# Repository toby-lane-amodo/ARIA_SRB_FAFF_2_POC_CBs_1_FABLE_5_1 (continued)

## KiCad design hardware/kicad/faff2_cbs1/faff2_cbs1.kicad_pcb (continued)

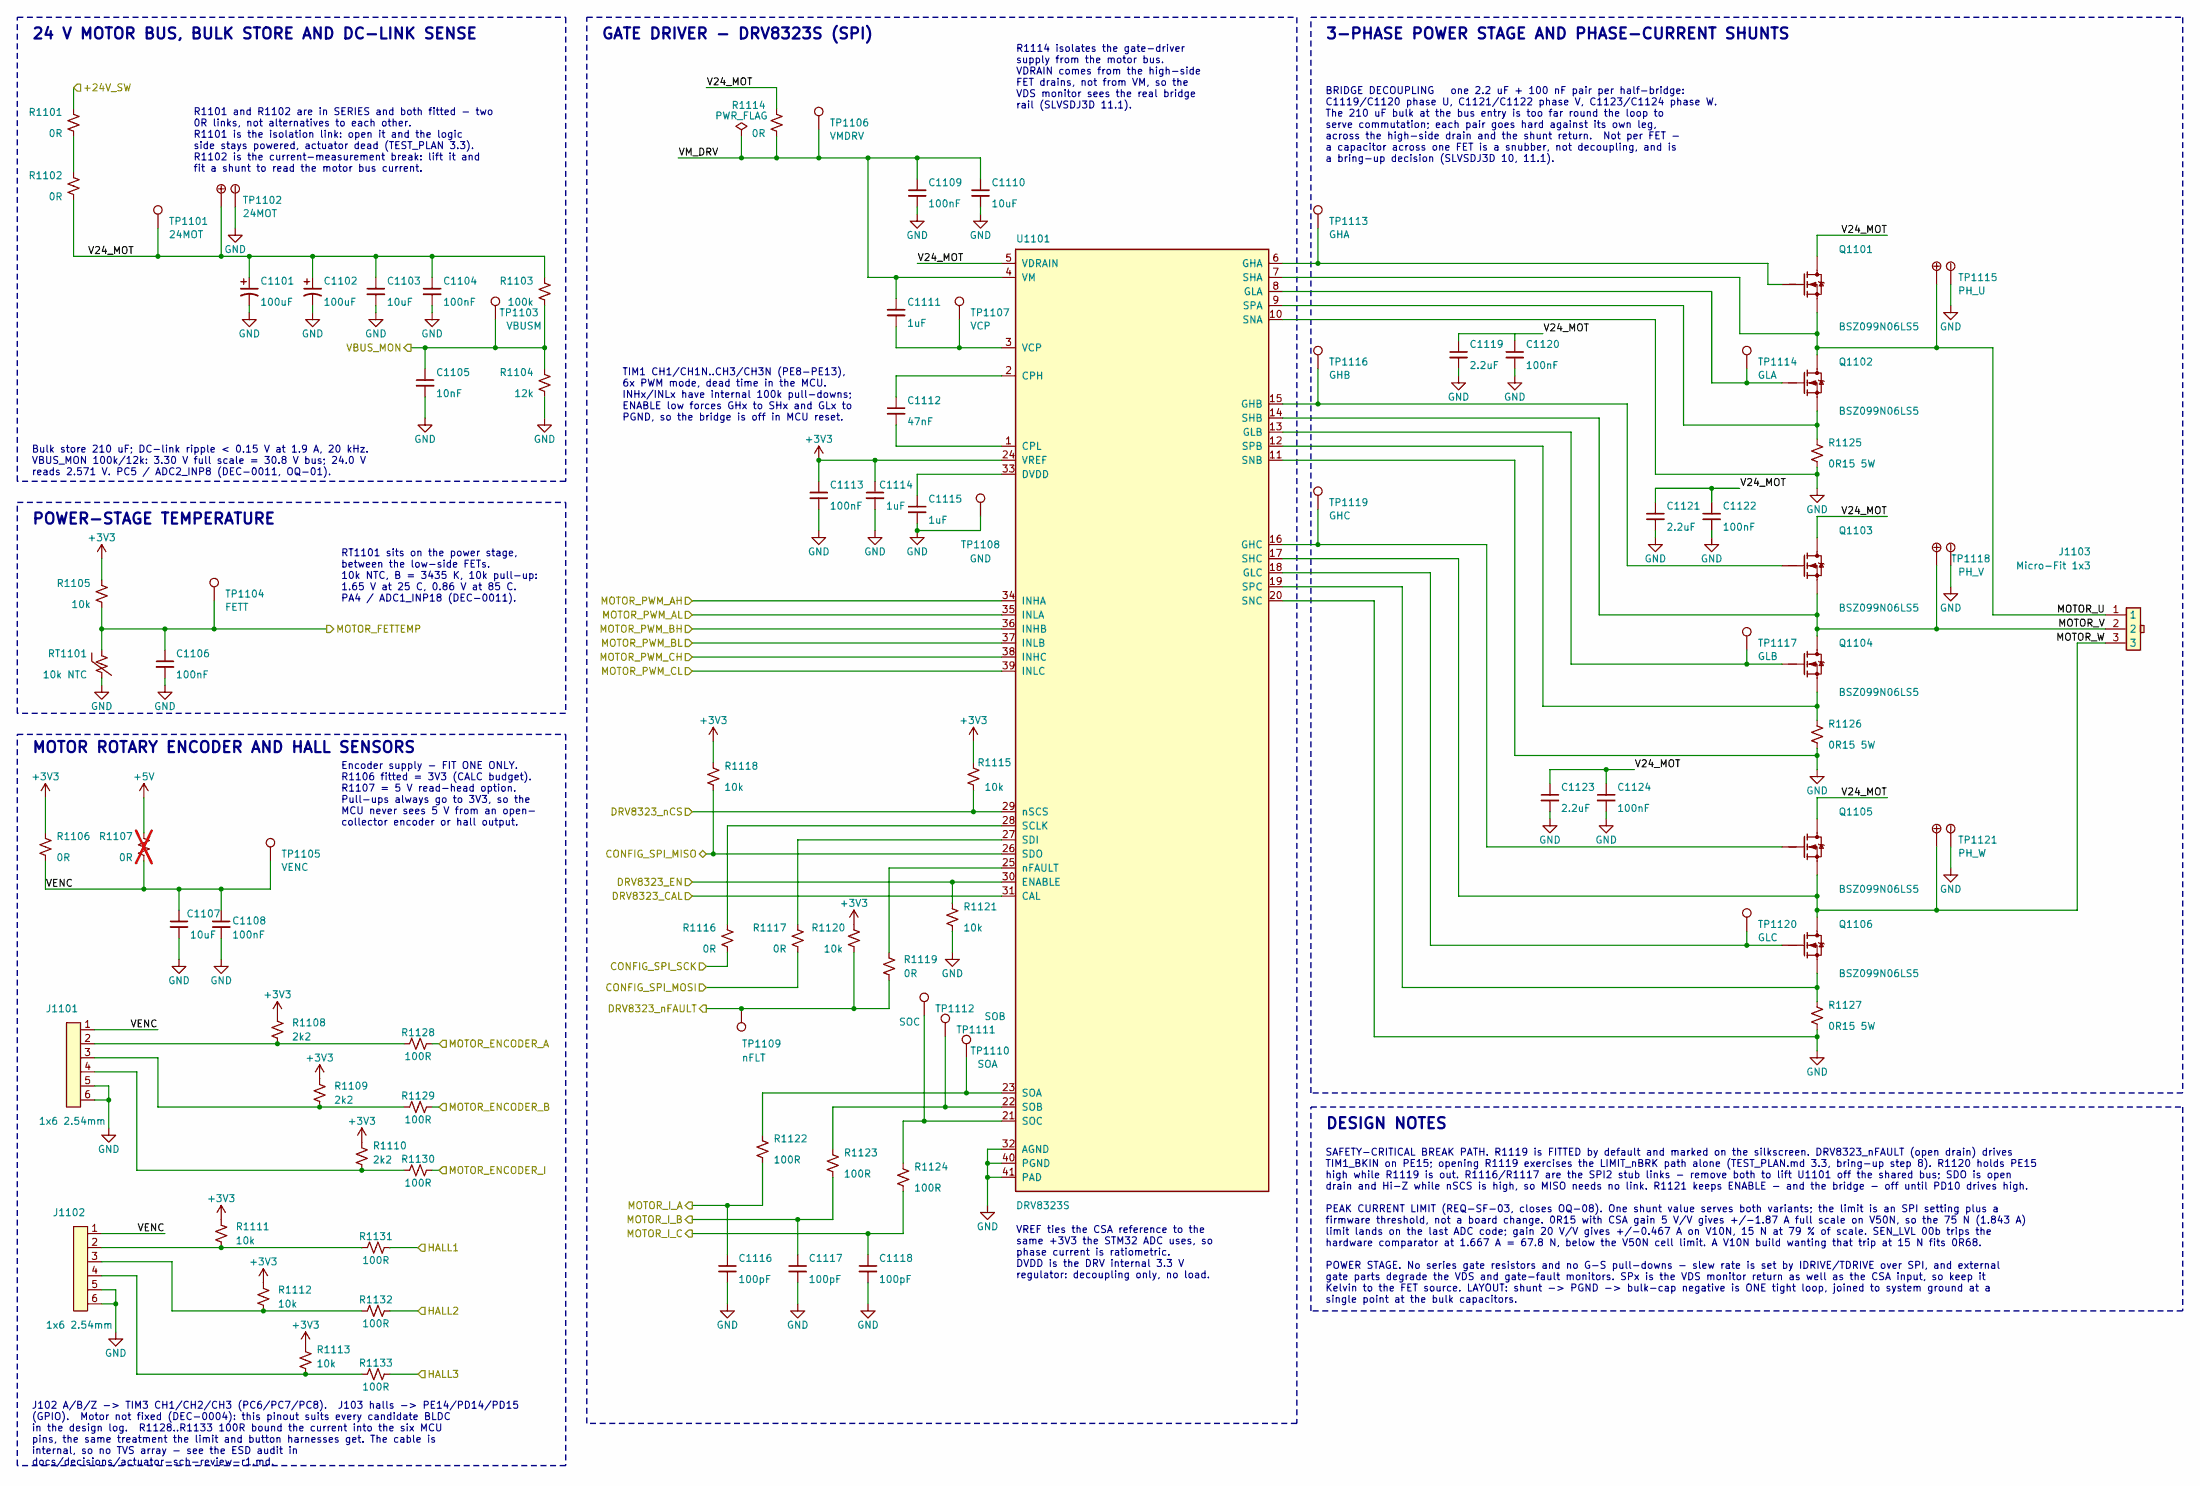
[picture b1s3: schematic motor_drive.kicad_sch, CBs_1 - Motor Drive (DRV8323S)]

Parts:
C1101, C1102: 100uF; C_ALU_D10_L10.2_SMT_ANTI-VIBE
C1103, C1110: 10uF; C_1210_3225Metric
C1104, C1109: 100nF; C_0805_2012Metric
C1105: 10nF; C_0603_1608Metric
C1106, C1108, C1113: 100nF; C_0402_1005Metric
C1107: 10uF; C_0805_2012Metric
C1111, C1114, C1115: 1uF; C_0603_1608Metric
C1112: 47nF; C_0603_1608Metric
C1116, C1117, C1118: 100pF; C_0603_1608Metric
C1119, C1121, C1123: 2.2uF; C_1206_3216Metric; mpn KAM31GR72A225KU
C1120, C1122, C1124: 100nF; C_0805_2012Metric; Voltage 100V; mpn 08051C104K4T4A
J1101, J1102: 1x6 2.54mm; Adam_Tech_PH1-06-UA
J1103: Micro-Fit 1x3; 436500327
Q1101, Q1102, Q1103, Q1104, Q1105, Q1106: BSZ099N06LS5; PG-TSDSON-8-32
R1101, R1102, R1114: 0R; R_1206_3216Metric
R1103: 100k; R_0603_1608Metric
R1104: 12k; R_0603_1608Metric
R1105, R1111, R1112, R1113, R1115, R1118, R1120, R1121: 10k; R_0603_1608Metric
R1106, R1116, R1117, R1119: 0R; R_0603_1608Metric
R1107: 0R; R_0603_1608Metric; not fitted
R1108, R1109, R1110: 2k2; R_0603_1608Metric
R1122, R1123, R1124: 100R; R_0603_1608Metric
R1125, R1126, R1127: 0R15 5W; R_4527_11470Metric
R1128, R1129, R1130, R1131, R1132, R1133: 100R; R_0603_1608Metric; mpn ERJ-3EKF1000V
RT1101: 10k NTC; R_0603_1608Metric
TP1101: 24MOT; TestPoint_Pad_D1.0mm
TP1102: 24MOT; TestPoint_Dual_D1.5mm_H1.0mm
TP1103: VBUSM; TestPoint_Pad_D1.0mm
TP1104: FETT; TestPoint_Pad_D1.0mm
TP1105: VENC; TestPoint_Pad_D1.0mm
TP1106: VMDRV; TestPoint_Pad_D1.0mm
TP1107: VCP; TestPoint_Pad_D1.0mm
TP1108: GND; TestPoint_Pad_D1.0mm
TP1109: nFLT; KeystoneMiniatureTestLoop
TP1110: SOA; KeystoneMiniatureTestLoop
TP1111: SOB; KeystoneMiniatureTestLoop
TP1112: SOC; KeystoneMiniatureTestLoop
TP1113: GHA; KeystoneMiniatureTestLoop
TP1114: GLA; KeystoneMiniatureTestLoop
TP1115: PH_U; TestPoint_Dual_D1.5mm_H1.0mm
TP1116: GHB; KeystoneMiniatureTestLoop
TP1117: GLB; KeystoneMiniatureTestLoop
TP1118: PH_V; TestPoint_Dual_D1.5mm_H1.0mm
TP1119: GHC; KeystoneMiniatureTestLoop
TP1120: GLC; KeystoneMiniatureTestLoop
TP1121: PH_W; TestPoint_Dual_D1.5mm_H1.0mm
U1101: DRV8323S; Texas_RTA0040B_WQFN-40-1EP_6x6mm_P0.5mm_EP4.15x4.15mm

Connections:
+3V3: C1113.1, C1114.1, R1105.1, R1106.1, R1108.1, R1109.1, R1110.1, R1111.1, R1112.1, R1113.1, R1115.1, R1118.1, R1120.1, U1101.24 (VREF); also elsewhere on the board
+5V: R1107.1; also elsewhere on the board
/mcu/DRV8323_CAL: U1101.31 (CAL); also elsewhere on the board
/mcu/DRV8323_EN: R1121.1, U1101.30 (ENABLE); also elsewhere on the board
/mcu/DRV8323_nCS: R1115.2, U1101.29 (nSCS); also elsewhere on the board
/mcu/DRV8323_nFAULT: R1119.2, R1120.2, TP1109.1; also elsewhere on the board
/mcu/HALL1: R1131.2; also elsewhere on the board
/mcu/HALL2: R1132.2; also elsewhere on the board
/mcu/HALL3: R1133.2; also elsewhere on the board
/mcu/MOTOR_ENCODER_A: R1128.2; also elsewhere on the board
/mcu/MOTOR_ENCODER_B: R1129.2; also elsewhere on the board
/mcu/MOTOR_ENCODER_I: R1130.2; also elsewhere on the board
/mcu/MOTOR_FETTEMP: C1106.1, R1105.2, RT1101.1, TP1104.1; also elsewhere on the board
/mcu/MOTOR_I_A: C1116.1, R1122.2; also elsewhere on the board
/mcu/MOTOR_I_B: C1117.1, R1123.2; also elsewhere on the board
/mcu/MOTOR_I_C: C1118.1, R1124.2; also elsewhere on the board
/mcu/MOTOR_PWM_AH: U1101.34 (INHA); also elsewhere on the board
/mcu/MOTOR_PWM_AL: U1101.35 (INLA); also elsewhere on the board
/mcu/MOTOR_PWM_BH: U1101.36 (INHB); also elsewhere on the board
/mcu/MOTOR_PWM_BL: U1101.37 (INLB); also elsewhere on the board
/mcu/MOTOR_PWM_CH: U1101.38 (INHC); also elsewhere on the board
/mcu/MOTOR_PWM_CL: U1101.39 (INLC); also elsewhere on the board
/mcu/VBUS_MON: C1105.1, R1103.2, R1104.1, TP1103.1; also elsewhere on the board
/motor_drive/MOTOR_U: J1103.1, Q1101.1_2_3 (S_3), Q1102.5_6_7_8 (D_2), TP1115.1, U1101.7 (SHA)
/motor_drive/MOTOR_V: J1103.2, Q1103.1_2_3 (S_3), Q1104.5_6_7_8 (D_2), TP1118.1, U1101.14 (SHB)
/motor_drive/MOTOR_W: J1103.3, Q1105.1_2_3 (S_3), Q1106.5_6_7_8 (D_2), TP1121.1, U1101.17 (SHC)
/motor_drive/V24_MOT: C1101.1, C1102.1, C1103.1, C1104.1, C1119.1, C1120.1, C1121.1, C1122.1, C1123.1, C1124.1, Q1101.5_6_7_8 (D_2), Q1103.5_6_7_8 (D_2), Q1105.5_6_7_8 (D_2), R1102.2, R1103.1, R1114.1, TP1101.1, TP1102.1, U1101.5 (VDRAIN)
/motor_drive/VENC: C1107.1, C1108.1, J1101.1, J1102.1, R1106.2, R1107.2, TP1105.1
/motor_drive/VM_DRV: C1109.1, C1110.1, C1111.1, R1114.2, TP1106.1, U1101.4 (VM)
/power_entry_24v/+24V_SW: R1101.1; also elsewhere on the board
/temp_sense/CONFIG_SPI_MISO: R1118.2, U1101.26 (SDO); also elsewhere on the board
/temp_sense/CONFIG_SPI_MOSI: R1117.2; also elsewhere on the board
/temp_sense/CONFIG_SPI_SCK: R1116.2; also elsewhere on the board
GND: C1101.2, C1102.2, C1103.2, C1104.2, C1105.2, C1106.2, C1107.2, C1108.2, C1109.2, C1110.2, C1113.2, C1114.2, C1115.2, C1116.2, C1117.2, C1118.2, C1119.2, C1120.2, C1121.2, C1122.2, C1123.2, C1124.2, J1101.5, J1101.6, J1102.5, J1102.6, R1104.2, R1121.2, R1125.2, R1126.2, R1127.2, RT1101.2, TP1102.2, TP1108.1, TP1115.2, TP1118.2, TP1121.2, U1101.10 (SNA), U1101.11 (SNB), U1101.20 (SNC), U1101.32 (AGND), U1101.40 (PGND), U1101.41 (PAD); also elsewhere on the board
unnamed: J1101.2, R1108.2, R1128.1
unnamed: J1101.3, R1109.2, R1129.1
unnamed: J1101.4, R1110.2, R1130.1
unnamed: J1102.2, R1111.2, R1131.1
unnamed: J1102.3, R1112.2, R1132.1
unnamed: J1102.4, R1113.2, R1133.1
unnamed: Q1101.4 (G), TP1113.1, U1101.6 (GHA)
unnamed: Q1102.4 (G), TP1114.1, U1101.8 (GLA)
unnamed: Q1102.1_2_3 (S_3), R1125.1, U1101.9 (SPA)
unnamed: Q1103.4 (G), TP1116.1, U1101.15 (GHB)
unnamed: Q1104.4 (G), TP1117.1, U1101.13 (GLB)
unnamed: Q1104.1_2_3 (S_3), R1126.1, U1101.12 (SPB)
unnamed: Q1105.4 (G), TP1119.1, U1101.16 (GHC)
unnamed: Q1106.4 (G), TP1120.1, U1101.18 (GLC)
unnamed: Q1106.1_2_3 (S_3), R1127.1, U1101.19 (SPC)
unnamed: R1101.2, R1102.1
unnamed: C1112.1, U1101.2 (CPH)
unnamed: C1112.2, U1101.1 (CPL)
unnamed: C1115.1, U1101.33 (DVDD)
unnamed: R1116.1, U1101.28 (SCLK)
unnamed: R1117.1, U1101.27 (SDI)
unnamed: R1122.1, TP1110.1, U1101.23 (SOA)
unnamed: R1123.1, TP1111.1, U1101.22 (SOB)
unnamed: R1124.1, TP1112.1, U1101.21 (SOC)
unnamed: C1111.2, TP1107.1, U1101.3 (VCP)
unnamed: R1119.1, U1101.25 (nFAULT)

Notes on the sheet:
BRIDGE DECOUPLING one 2.2 uF + 100 nF pair per half-bridge: C1119/C1120 phase U, C1121/C1122 phase V, C1123/C1124 phase W. The 210 uF bulk at the bus entry is too far round the loop to serve commutation; each pair goes hard against its own leg, across the high-side drain and the shunt return. Not p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
Bulk store 210 uF; DC-link ripple < 0.15 V at 1.9 A, 20 kHz. VBUS_MON 100k/12k: 3.30 V full scale = 30.8 V bus; 24.0 V reads 2.571 V. PC5 / ADC2_INP8 (DEC-0011, OQ-01).
SAFETY-CRITICAL BREAK PATH. R1119 is FITTED by default and marked on the silkscreen. DRV8323_nFAULT (open drain) drives TIM1_BKIN on PE15; opening R1119 exercises the LIMIT_nBRK path alone (TEST_PLAN.md 3.3, bring-up step 8). R1120 holds PE15 high while R1119 is out. R1116/R1117 are the SPI2 stub l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
RT1101 sits on the power stage, between the low-side FETs. 10k NTC, B = 3435 K, 10k pull-up: 1.65 V at 25 C, 0.86 V at 85 C. PA4 / ADC1_INP18 (DEC-0011).
Encoder supply - FIT ONE ONLY. R1106 fitted = 3V3 (CALC budget). R1107 = 5 V read-head option. Pull-ups always go to 3V3, so the MCU never sees 5 V from an open- collector encoder or hall output.
J102 A/B/Z -> TIM3 CH1/CH2/CH3 (PC6/PC7/PC8). J103 halls -> PE14/PD14/PD15 (GPIO). Motor not fixed (DEC-0004): this pinout suits every candidate BLDC in the design log. R1128..R1133 100R bound the current into the six MCU pins, the same treatment the limit and button harnesses get. The cable is int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
MOTOR ROTARY ENCODER AND HALL SENSORS
R1101 and R1102 are in SERIES and both fitted - two 0R links, not alternatives to each other. R1101 is the isolation link: open it and the logic side stays powered, actuator dead (TEST_PLAN 3.3). R1102 is the current-measurement break: lift it and fit a shunt to read the motor bus current.
DESIGN NOTES
24 V MOTOR BUS, BULK STORE AND DC-LINK SENSE
TIM1 CH1/CH1N..CH3/CH3N (PE8-PE13), 6x PWM mode, dead time in the MCU. INHx/INLx have internal 100k pull-downs; ENABLE low forces GHx to SHx and GLx to PGND, so the bridge is off in MCU reset.
POWER-STAGE TEMPERATURE
VREF ties the CSA reference to the same +3V3 the STM32 ADC uses, so phase current is ratiometric. DVDD is the DRV internal 3.3 V regulator: decoupling only, no load.
R1114 isolates the gate-driver supply from the motor bus. VDRAIN comes from the high-side FET drains, not from VM, so the VDS monitor sees the real bridge rail (SLVSDJ3D 11.1).
GATE DRIVER - DRV8323S (SPI)
3-PHASE POWER STAGE AND PHASE-CURRENT SHUNTS

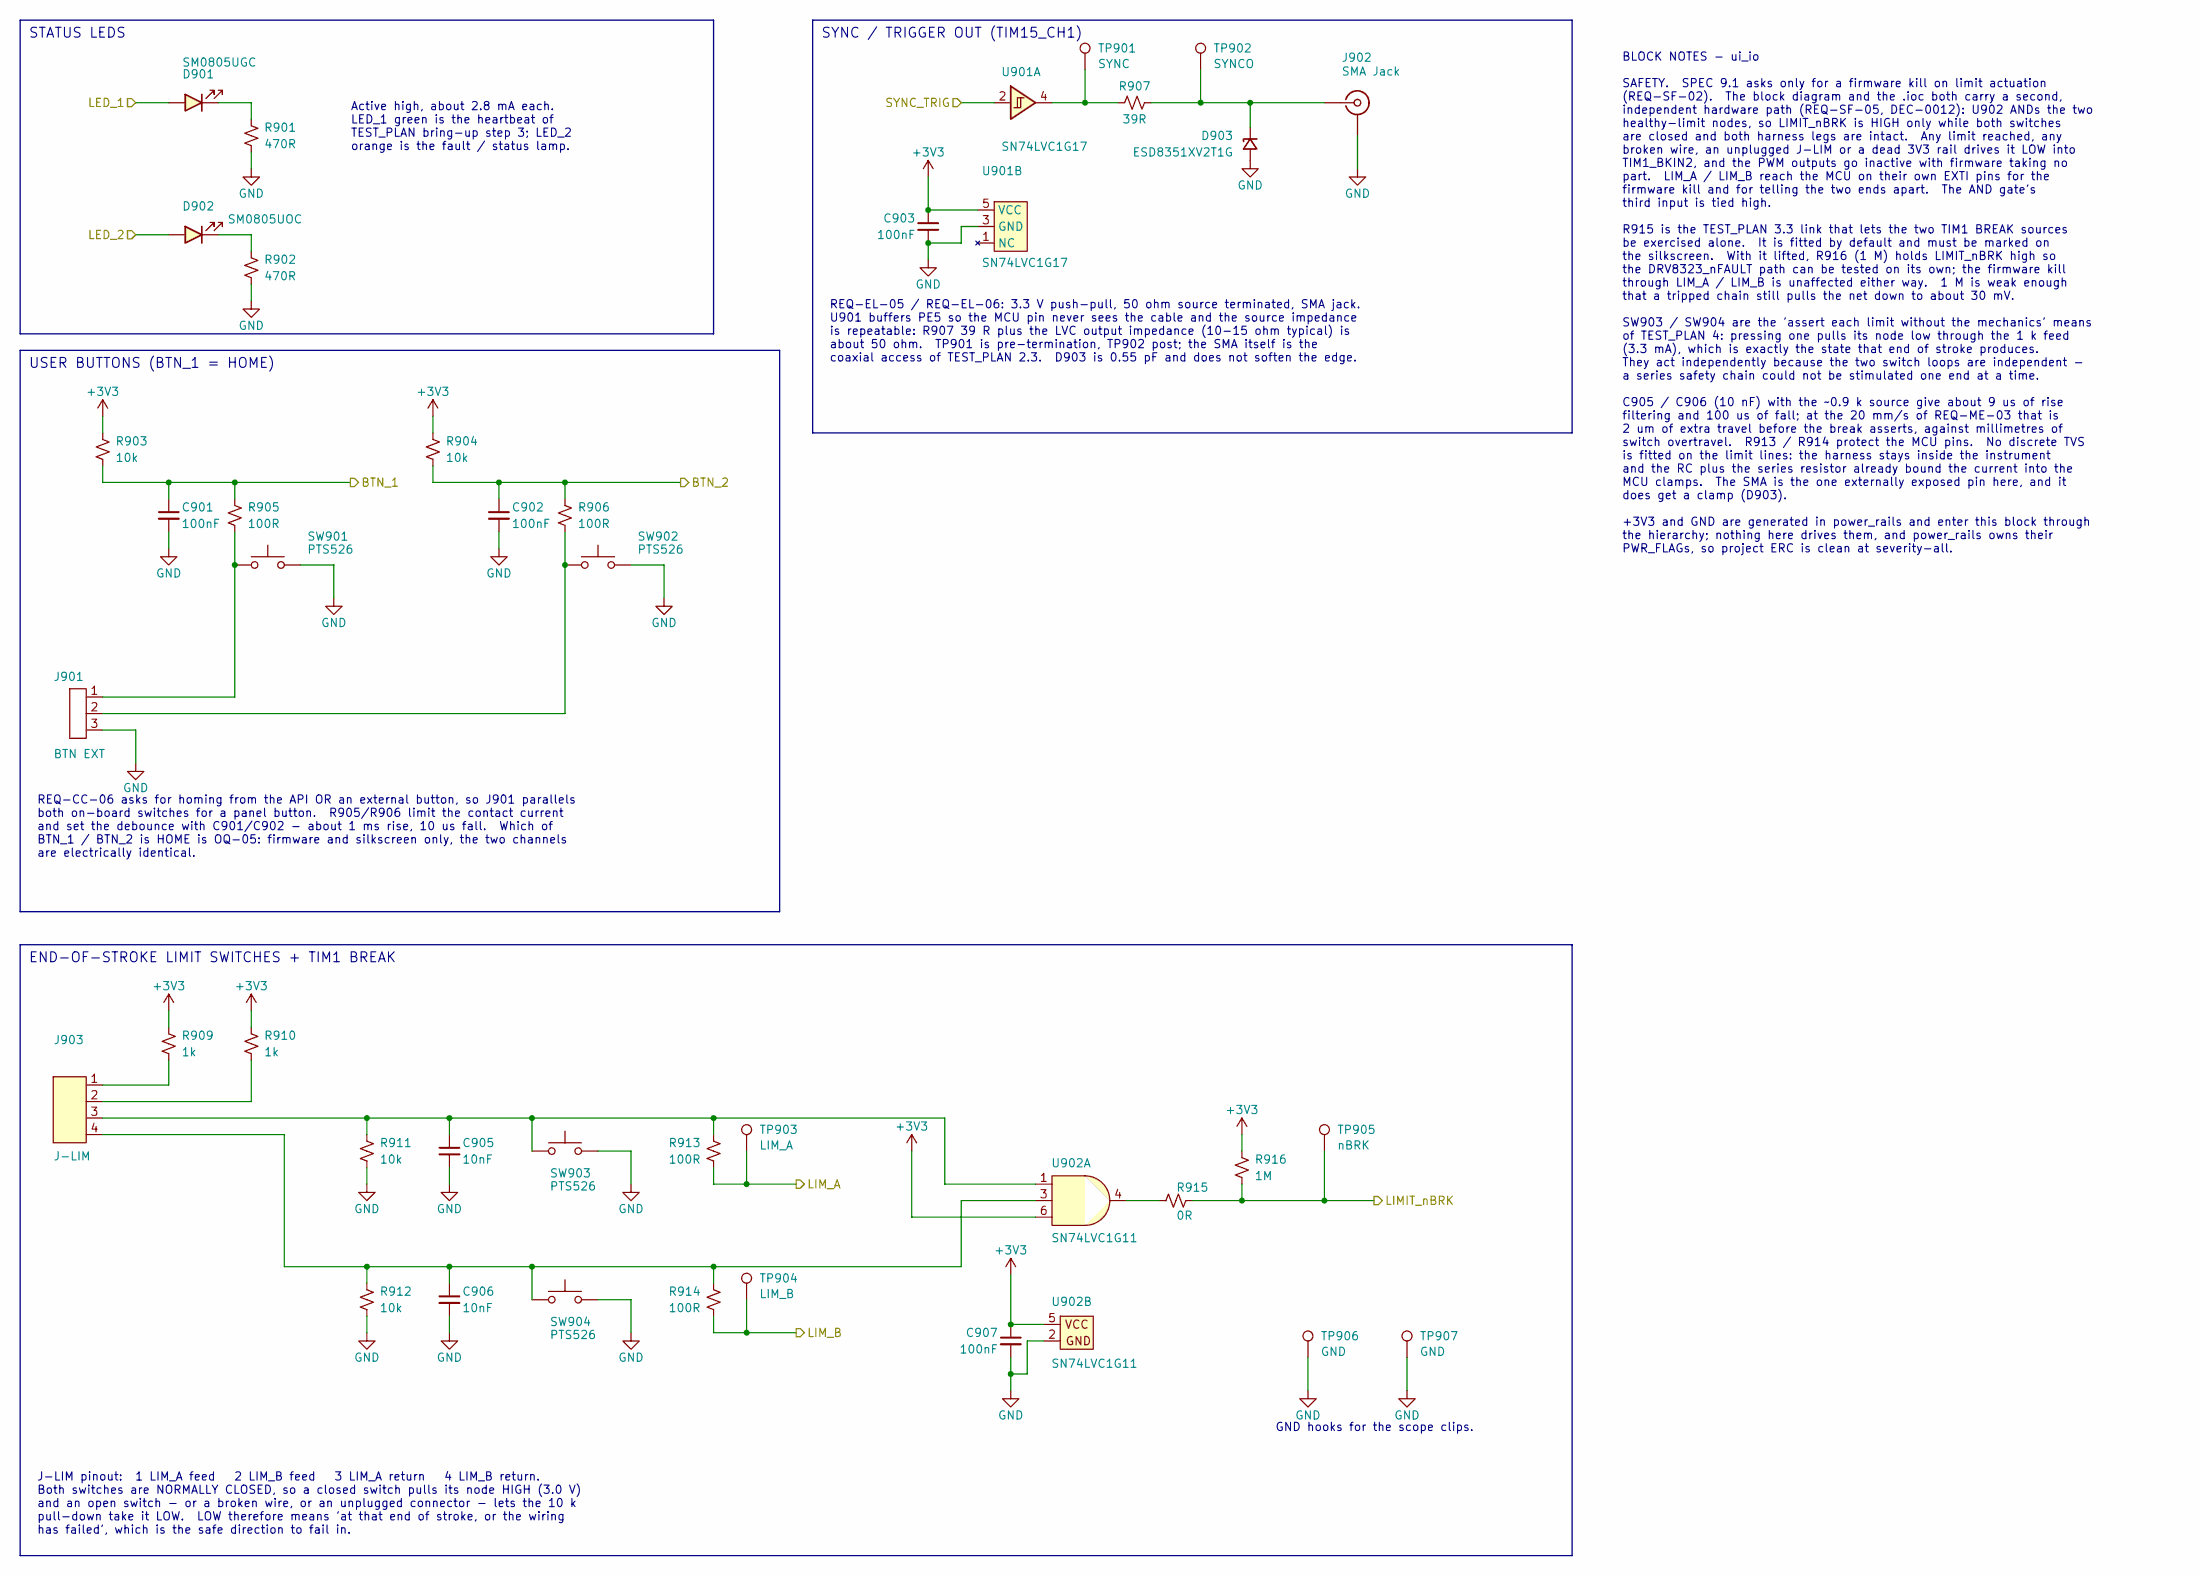
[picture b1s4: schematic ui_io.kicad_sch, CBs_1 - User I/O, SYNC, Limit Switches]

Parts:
C901, C902, C903, C907: 100nF; C_0603_1608Metric; mpn C0603C104M5RACAUTO
C905, C906: 10nF; C_0603_1608Metric; mpn C0603C103M5RACAUTO
D901: SM0805UGC; LED 0805 SM0805; mpn SM0805UGC
D902: SM0805UOC; LED 0805 SM0805; mpn SM0805UOC
D903: ESD8351XV2T1G; SC-79 (SOD523); mpn ESD8351XV2T1G
J901: BTN EXT; 87224-3; mpn 87224-3
J902: SMA Jack; SMA-J-P-H-ST-TH1; mpn SMA-J-P-H-ST-TH1
J903: J-LIM; B4B-XH-AM; mpn B4B-XH-AM
R901, R902: 470R; R_0603_1608Metric; mpn ERJ-3EKF4700V
R903, R904, R911, R912: 10k; R_0603_1608Metric; mpn ERJ-3EKF1002V
R905, R906, R913, R914: 100R; R_0603_1608Metric; mpn ERJ-3EKF1000V
R907: 39R; R_0603_1608Metric; mpn ERJ-3EKF39R0V
R909, R910: 1k; R_0603_1608Metric; mpn CR0603AFX-1001ELF
R915: 0R; R_0603_1608Metric; mpn RC0603FR-070RL
R916: 1M; R_0603_1608Metric; mpn ERJ-3EKF1004V
SW901, SW902, SW903, SW904: PTS526; PTS526_1.5mm_G; mpn PTS526 SK15 SMTR2 LFS
TP901: SYNC; KeystoneMiniatureTestLoop; mpn 5002
TP902: SYNCO; TestPoint_Pad_D1.0mm
TP903: LIM_A; KeystoneMiniatureTestLoop; mpn 5002
TP904: LIM_B; KeystoneMiniatureTestLoop; mpn 5002
TP905: nBRK; KeystoneMiniatureTestLoop; mpn 5002
TP906, TP907: GND; KeystoneMiniatureTestLoop; mpn 5002
U901: SN74LVC1G17; SOT23-5 - TI; mpn SN74LVC1G17DBVRG4
U902: SN74LVC1G11; SOT23-6; mpn SN74LVC1G11DBVR

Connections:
+3V3: C903.1, C907.1, R903.1, R904.1, R909.1, R910.1, R916.1, U901.5 (VCC), U902.5 (VCC), U902.6 (C); also elsewhere on the board
/mcu/BTN_1: C901.1, R903.2, R905.1; also elsewhere on the board
/mcu/BTN_2: C902.1, R904.2, R906.1; also elsewhere on the board
/mcu/LED_1: D901.1; also elsewhere on the board
/mcu/LED_2: D902.1; also elsewhere on the board
/mcu/LIMIT_nBRK: R915.2, R916.2, TP905.1; also elsewhere on the board
/mcu/LIM_A: R913.2, TP903.1; also elsewhere on the board
/mcu/LIM_B: R914.2, TP904.1; also elsewhere on the board
/mcu/SYNC_TRIG: U901.2; also elsewhere on the board
GND: C901.2, C902.2, C903.2, C905.2, C906.2, C907.2, D903.2 (A), J901.3, J902.2 (Ext), R901.2, R902.2, R911.2, R912.2, SW901.3_4, SW902.3_4, SW903.3_4, SW904.3_4, TP906.1, TP907.1, U901.3 (GND), U902.2 (GND); also elsewhere on the board
unnamed: D901.2, R901.1
unnamed: D902.2, R902.1
unnamed: D903.1 (K), J902.1 (In), R907.2, TP902.1
unnamed: J901.1, R905.2, SW901.1_2
unnamed: J901.2, R906.2, SW902.1_2
unnamed: J903.1, R909.2
unnamed: J903.2, R910.2
unnamed: R907.1, TP901.1, U901.4
unnamed: C905.1, J903.3, R911.1, R913.1, SW903.1_2, U902.1 (A)
unnamed: C906.1, J903.4, R912.1, R914.1, SW904.1_2, U902.3 (B)
unnamed: R915.1, U902.4 (Y)

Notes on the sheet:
GND hooks for the scope clips.
J-LIM pinout: 1 LIM_A feed 2 LIM_B feed 3 LIM_A return 4 LIM_B return. Both switches are NORMALLY CLOSED, so a closed switch pulls its node HIGH (3.0 V) and an open switch - or a broken wire, or an unplugged connector - lets the 10 k pull-down take it LOW. LOW therefore means 'at that end of stroke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
STATUS LEDS
REQ-EL-05 / REQ-EL-06: 3.3 V push-pull, 50 ohm source terminated, SMA jack. U901 buffers PE5 so the MCU pin never sees the cable and the source impedance is repeatable: R907 39 R plus the LVC output impedance (10-15 ohm typical) is about 50 ohm. TP901 is pre-termination, TP902 post; the SMA itself 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
END-OF-STROKE LIMIT SWITCHES + TIM1 BREAK
BLOCK NOTES - ui_io SAFETY. SPEC 9.1 asks only for a firmware kill on limit actuation (REQ-SF-02). The block diagram and the .ioc both carry a second, independent hardware path (REQ-SF-05, DEC-0012): U902 ANDs the two healthy-limit nodes, so LIMIT_nBRK is HIGH only while both switches are closed an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
Active high, about 2.8 mA each. LED_1 green is the heartbeat of TEST_PLAN bring-up step 3; LED_2 orange is the fault / status lamp.
USER BUTTONS (BTN_1 = HOME)
REQ-CC-06 asks for homing from the API OR an external button, so J901 parallels both on-board switches for a panel button. R905/R906 limit the contact current and set the debounce with C901/C902 - about 1 ms rise, 10 us fall. Which of BTN_1 / BTN_2 is HOME is OQ-05: firmware and silkscreen only, th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
SYNC / TRIGGER OUT (TIM15_CH1)

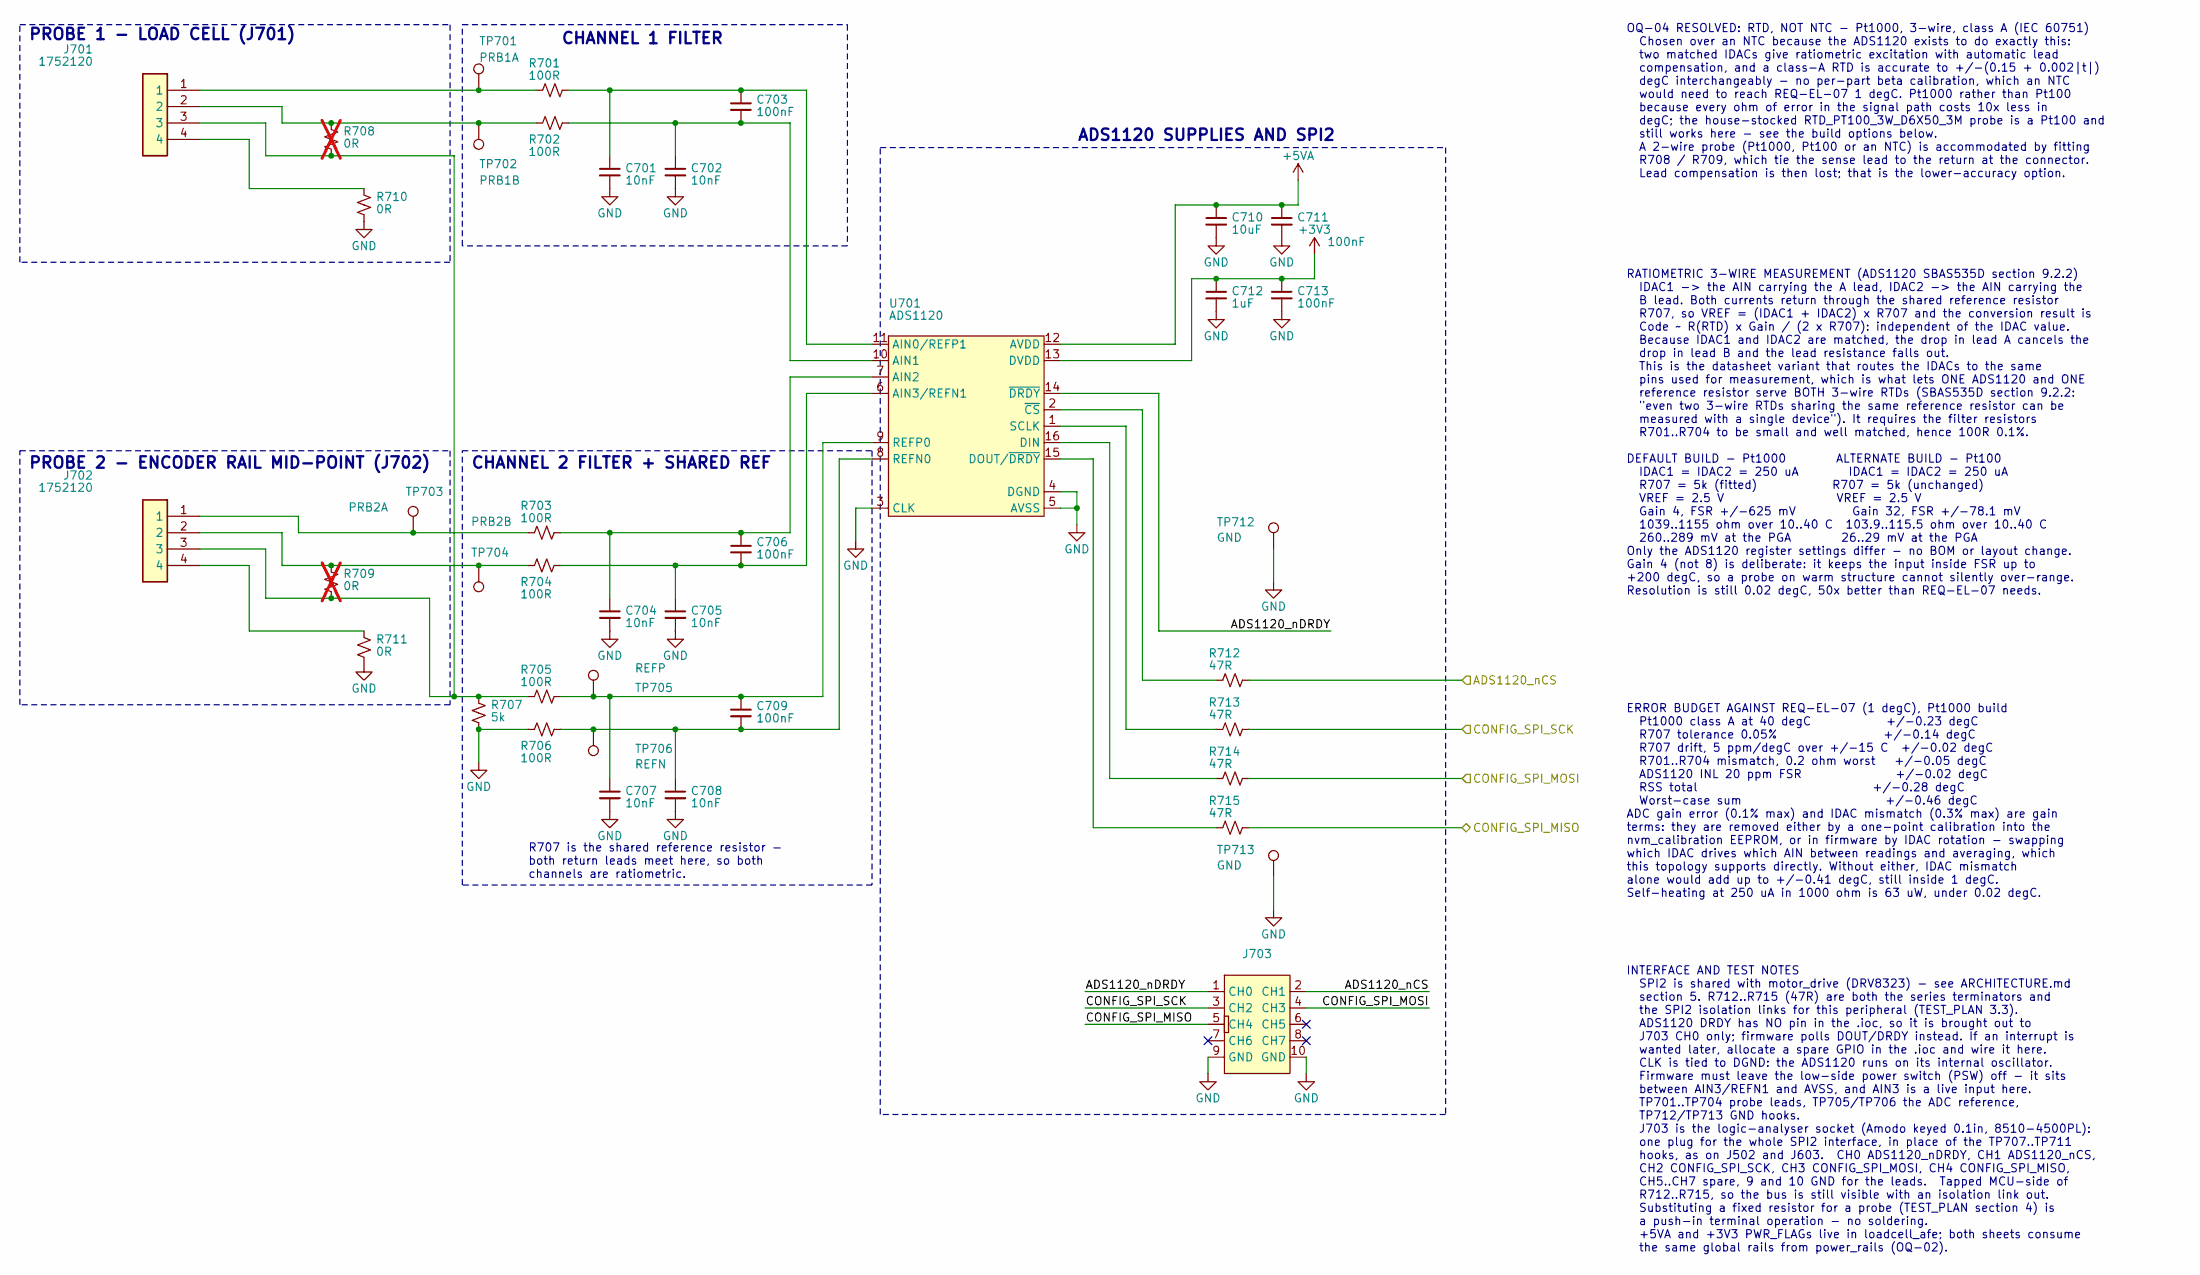
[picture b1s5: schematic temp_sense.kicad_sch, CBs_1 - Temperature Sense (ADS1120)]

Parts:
C701, C702, C704, C705, C707, C708: 10nF; C_0603_1608Metric; mpn CGA3EAC0G2A103J080AC
C703, C706, C709, C711, C713: 100nF; C_0402_1005Metric; mpn 04025C104KAT2A
C710: 10uF; C_0805_2012Metric; mpn GRM21BR61E106MA73L
C712: 1uF; C_0603_1608Metric; mpn CL10B105KO8NNNC
J701, J702: 1752120; SHDR4W100P0X350_1X4_1460X1000X1240P; mpn 1752120
J703: 8510-4500PL; 8510-4500PL_LOGIC_TEST; mpn 8510-4500PL
R701, R702, R703, R704, R705, R706: 100R; R_0603_1608Metric; mpn ERA3AEB101V
R707: 5k; R_0805_2012Metric; mpn PLT0805Z5001AST5
R708, R709: 0R; R_0603_1608Metric; mpn RC0603FR-070RL; not fitted
R710, R711: 0R; R_0603_1608Metric; mpn RC0603FR-070RL
R712, R713, R714, R715: 47R; R_0603_1608Metric; mpn ERJ-3EKF47R0V
TP701: PRB1A; TestPoint_Pad_D1.0mm
TP702: PRB1B; TestPoint_Pad_D1.0mm
TP703: PRB2A; TestPoint_Pad_D1.0mm
TP704: PRB2B; TestPoint_Pad_D1.0mm
TP705: REFP; TestPoint_Pad_D1.0mm
TP706: REFN; TestPoint_Pad_D1.0mm
TP712, TP713: GND; KeystoneMiniatureTestLoop; mpn 5002
U701: ADS1120; TSSOP-16; mpn ADS1120IPWR

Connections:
+3V3: C712.1, C713.1, U701.13 (DVDD); also elsewhere on the board
+5VA: C710.1, C711.1, U701.12 (AVDD); also elsewhere on the board
/temp_sense/ADS1120_nCS: J703.2 (CH1), R712.2; also elsewhere on the board
/temp_sense/ADS1120_nDRDY: J703.1 (CH0), U701.14 (~DRDY)
/temp_sense/CONFIG_SPI_MISO: J703.5 (CH4), R715.2; also elsewhere on the board
/temp_sense/CONFIG_SPI_MOSI: J703.4 (CH3), R714.2; also elsewhere on the board
/temp_sense/CONFIG_SPI_SCK: J703.3 (CH2), R713.2; also elsewhere on the board
GND: C701.2, C702.2, C704.2, C705.2, C707.2, C708.2, C710.2, C711.2, C712.2, C713.2, J703.9 (GND), J703.10 (GND), R706.1, R707.2, R710.2, R711.2, TP712.1, TP713.1, U701.3 (CLK), U701.4 (DGND), U701.5 (AVSS); also elsewhere on the board
unnamed: J701.1, R701.1, TP701.1
unnamed: J701.2, R702.1, R708.1, TP702.1
unnamed: J701.3, J702.3, R705.1, R707.1, R708.2, R709.2
unnamed: J701.4, R710.1
unnamed: J702.1, R703.1, TP703.1
unnamed: J702.2, R704.1, R709.1, TP704.1
unnamed: J702.4, R711.1
unnamed: C701.1, C703.1, R701.2, U701.11 (AIN0/REFP1)
unnamed: C702.1, C703.2, R702.2, U701.10 (AIN1)
unnamed: C704.1, C706.1, R703.2, U701.7 (AIN2)
unnamed: C705.1, C706.2, R704.2, U701.6 (AIN3/REFN1)
unnamed: R714.1, U701.16 (DIN)
unnamed: R715.1, U701.15 (DOUT/~DRDY)
unnamed: C708.1, C709.2, R706.2, TP706.1, U701.8 (REFN0)
unnamed: C707.1, C709.1, R705.2, TP705.1, U701.9 (REFP0)
unnamed: R713.1, U701.1 (SCLK)
unnamed: R712.1, U701.2 (~CS)

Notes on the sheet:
ERROR BUDGET AGAINST REQ-EL-07 (1 degC), Pt1000 build Pt1000 class A at 40 degC +/-0.23 degC R707 tolerance 0.05% +/-0.14 degC R707 drift, 5 ppm/degC over +/-15 C +/-0.02 degC R701..R704 mismatch, 0.2 ohm worst +/-0.05 degC ADS1120 INL 20 ppm FSR +/-0.02 degC RSS total +/-0.28 degC Worst-case sum +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
ADS1120 SUPPLIES AND SPI2
RATIOMETRIC 3-WIRE MEASUREMENT (ADS1120 SBAS535D section 9.2.2) IDAC1 -> the AIN carrying the A lead, IDAC2 -> the AIN carrying the B lead. Both currents return through the shared reference resistor R707, so VREF = (IDAC1 + IDAC2) x R707 and the conversion result is Code ~ R(RTD) x Gain / (2 x R707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
PROBE 2 - ENCODER RAIL MID-POINT (J702)
OQ-04 RESOLVED: RTD, NOT NTC - Pt1000, 3-wire, class A (IEC 60751) Chosen over an NTC because the ADS1120 exists to do exactly this: two matched IDACs give ratiometric excitation with automatic lead compensation, and a class-A RTD is accurate to +/-(0.15 + 0.002|t|) degC interchangeably - no per-pa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
PROBE 1 - LOAD CELL (J701)
R707 is the shared reference resistor - both return leads meet here, so both channels are ratiometric.
CHANNEL 2 FILTER + SHARED REF
CHANNEL 1 FILTER
INTERFACE AND TEST NOTES SPI2 is shared with motor_drive (DRV8323) - see ARCHITECTURE.md section 5. R712..R715 (47R) are both the series terminators and the SPI2 isolation links for this peripheral (TEST_PLAN 3.3). ADS1120 DRDY has NO pin in the .ioc, so it is brought out to J703 CH0 only; firmware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

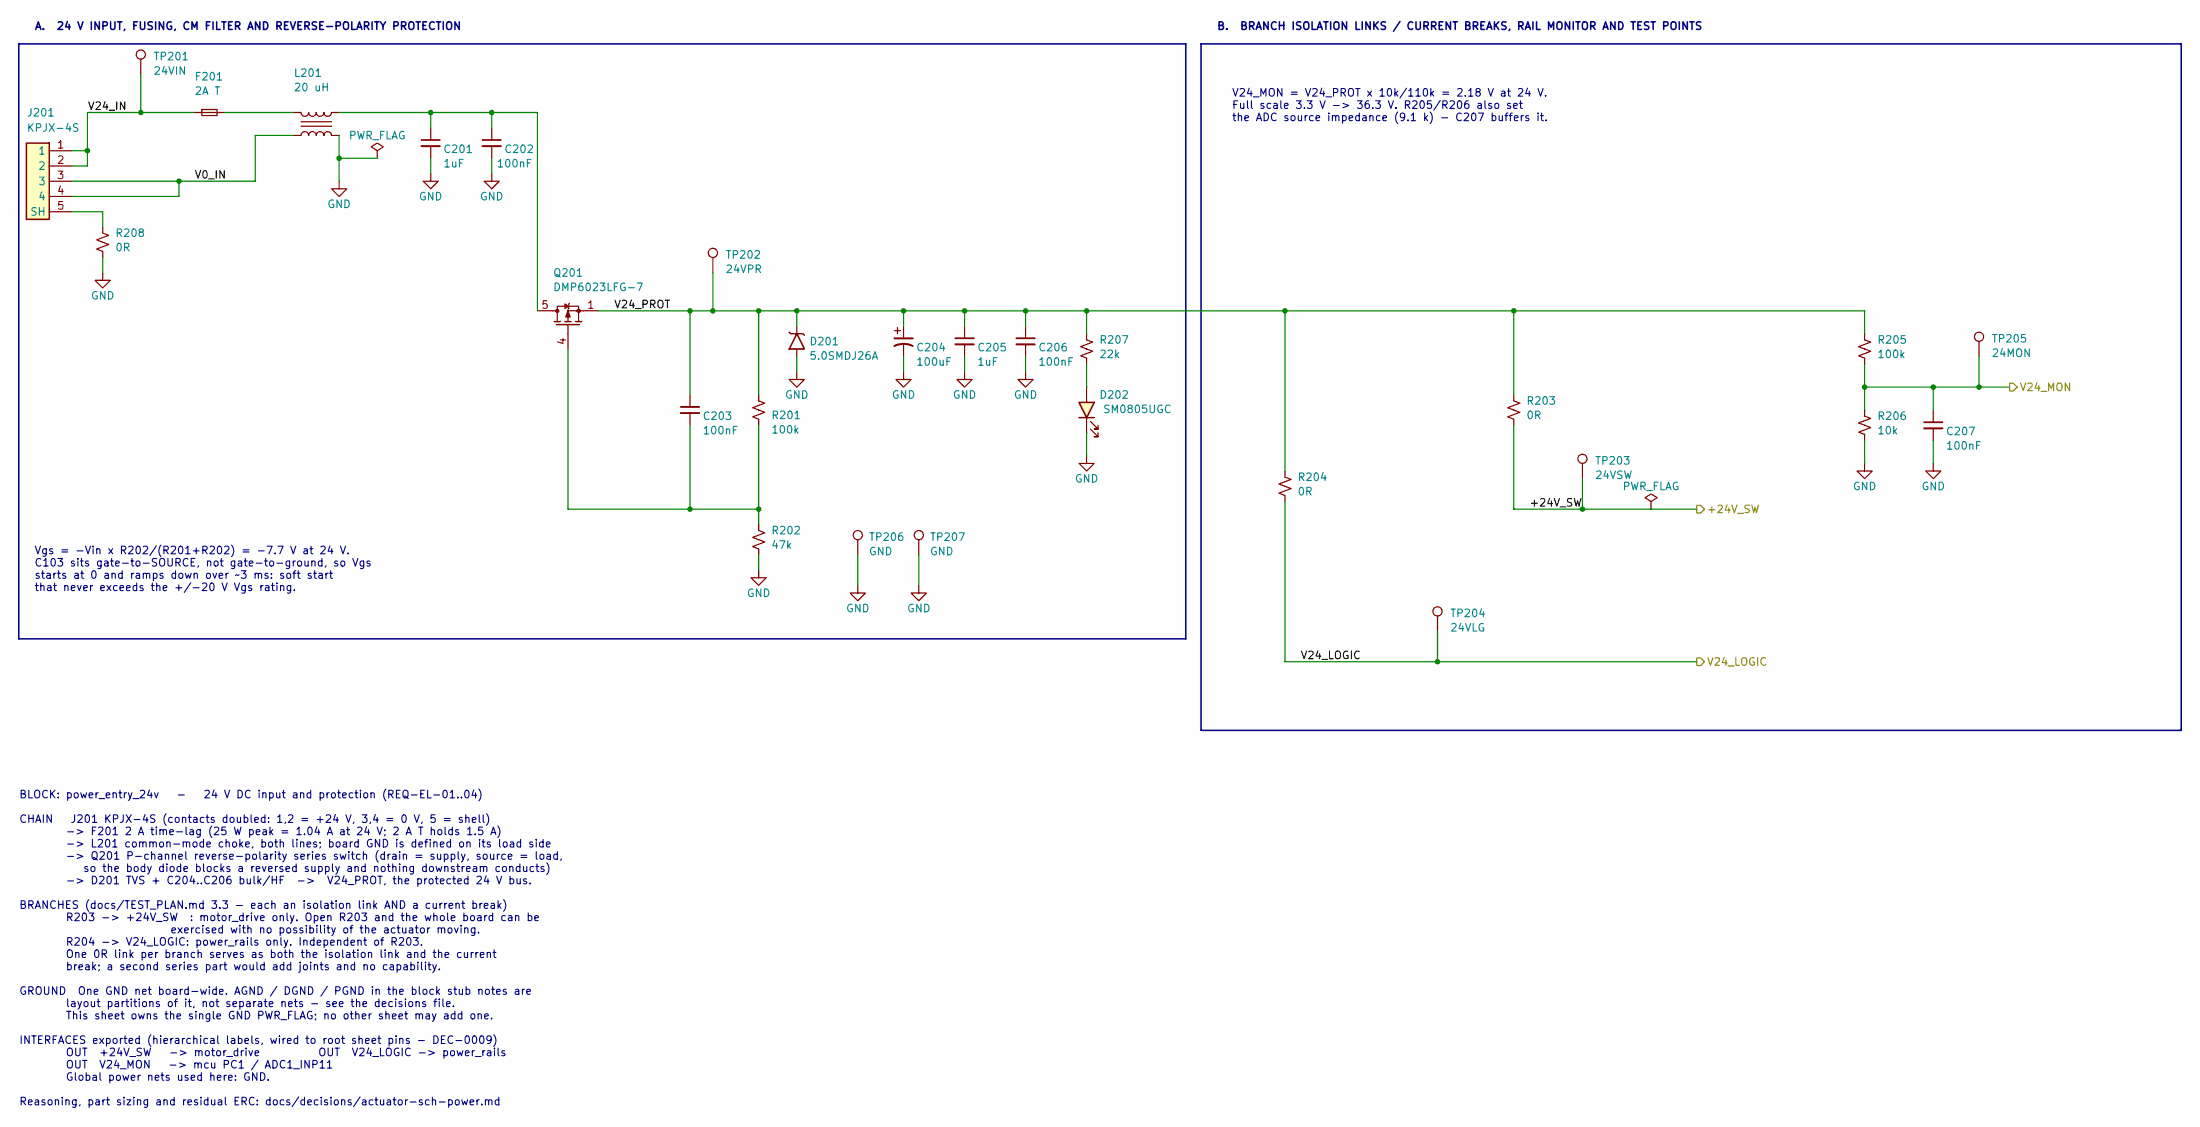
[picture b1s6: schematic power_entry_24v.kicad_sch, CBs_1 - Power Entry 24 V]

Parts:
C201, C205: 1uF; C_0805_2012Metric; Voltage 100V; mpn GRJ21BC72A105KE11L
C202, C206: 100nF; C_0805_2012Metric; Voltage 100V; mpn 08051C104K4T4A
C203, C207: 100nF; C_0603_1608Metric; mpn C0603C104M5RACAUTO
C204: 100uF; C_ALU_D10_L10.2_SMT_ANTI-VIBE; Voltage 63V; mpn EEE-FK1J101V
D201: 5.0SMDJ26A; DO-214AB; mpn 5.0SMDJ26A
D202: SM0805UGC; LED 0805 SM0805; mpn SM0805UGC
F201: 2A T; FUSE_157T_LittelFuse; mpn 0157002.DRT
J201: KPJX-4S; mpn KPJX-4S
L201: 20 uH; PLT10HH101150PN#; mpn PLT10HH1026R0PN#
Q201: DMP6023LFG-7; DMP4013LFG7; mpn DMP6023LFG-7
R201, R205: 100k; R_0603_1608Metric; mpn ERJ-3EKF1003V
R202: 47k; R_0603_1608Metric; mpn ERJ-3EKF4702V
R203, R204: 0R; R_1206_3216Metric; mpn PT1206-R-070RL
R206: 10k; R_0603_1608Metric; mpn ERJ-3EKF1002V
R207: 22k; R_0603_1608Metric; mpn ERJ-3EKF2202V
R208: 0R; R_0603_1608Metric; mpn RC0603FR-070RL
TP201: 24VIN; KeystoneMiniatureTestLoop; mpn 5002
TP202: 24VPR; KeystoneMiniatureTestLoop; mpn 5002
TP203: 24VSW; KeystoneMiniatureTestLoop; mpn 5002
TP204: 24VLG; KeystoneMiniatureTestLoop; mpn 5002
TP205: 24MON; TestPoint_Pad_D1.0mm
TP206, TP207: GND; KeystoneMiniatureTestLoop; mpn 5002

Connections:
/mcu/V24_MON: C207.1, R205.2, R206.1, TP205.1; also elsewhere on the board
/power_entry_24v/+24V_SW: R203.2, TP203.1; also elsewhere on the board
/power_entry_24v/V0_IN: J201.3, J201.4, L201.4
/power_entry_24v/V24_IN: F201.1, J201.1, J201.2, TP201.1
/power_entry_24v/V24_LOGIC: R204.2, TP204.1; also elsewhere on the board
/power_entry_24v/V24_PROT: C203.1, C204.1, C205.1, C206.1, D201.2 (A2), Q201.1 (S), R201.1, R203.1, R204.1, R205.1, R207.1, TP202.1
GND: C201.2, C202.2, C204.2, C205.2, C206.2, C207.2, D201.1 (A1), D202.2, L201.3, R202.2, R206.2, R208.2, TP206.1, TP207.1; also elsewhere on the board
unnamed: D202.1, R207.2
unnamed: F201.2, L201.1
unnamed: J201.5 (SH), R208.1
unnamed: C201.1, C202.1, L201.2, Q201.5 (D)
unnamed: C203.2, Q201.4 (G), R201.2, R202.1

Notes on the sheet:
Vgs = -Vin x R202/(R201+R202) = -7.7 V at 24 V. C103 sits gate-to-SOURCE, not gate-to-ground, so Vgs starts at 0 and ramps down over ~3 ms: soft start that never exceeds the +/-20 V Vgs rating.
A. 24 V INPUT, FUSING, CM FILTER AND REVERSE-POLARITY PROTECTION
BLOCK: power_entry_24v - 24 V DC input and protection (REQ-EL-01..04) CHAIN J201 KPJX-4S (contacts doubled: 1,2 = +24 V, 3,4 = 0 V, 5 = shell) -> F201 2 A time-lag (25 W peak = 1.04 A at 24 V; 2 A T holds 1.5 A) -> L201 common-mode choke, both lines; board GND is defined on its load side -> Q201 P-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
V24_MON = V24_PROT x 10k/110k = 2.18 V at 24 V. Full scale 3.3 V -> 36.3 V. R205/R206 also set the ADC source impedance (9.1 k) - C207 buffers it.
B. BRANCH ISOLATION LINKS / CURRENT BREAKS, RAIL MONITOR AND TEST POINTS
